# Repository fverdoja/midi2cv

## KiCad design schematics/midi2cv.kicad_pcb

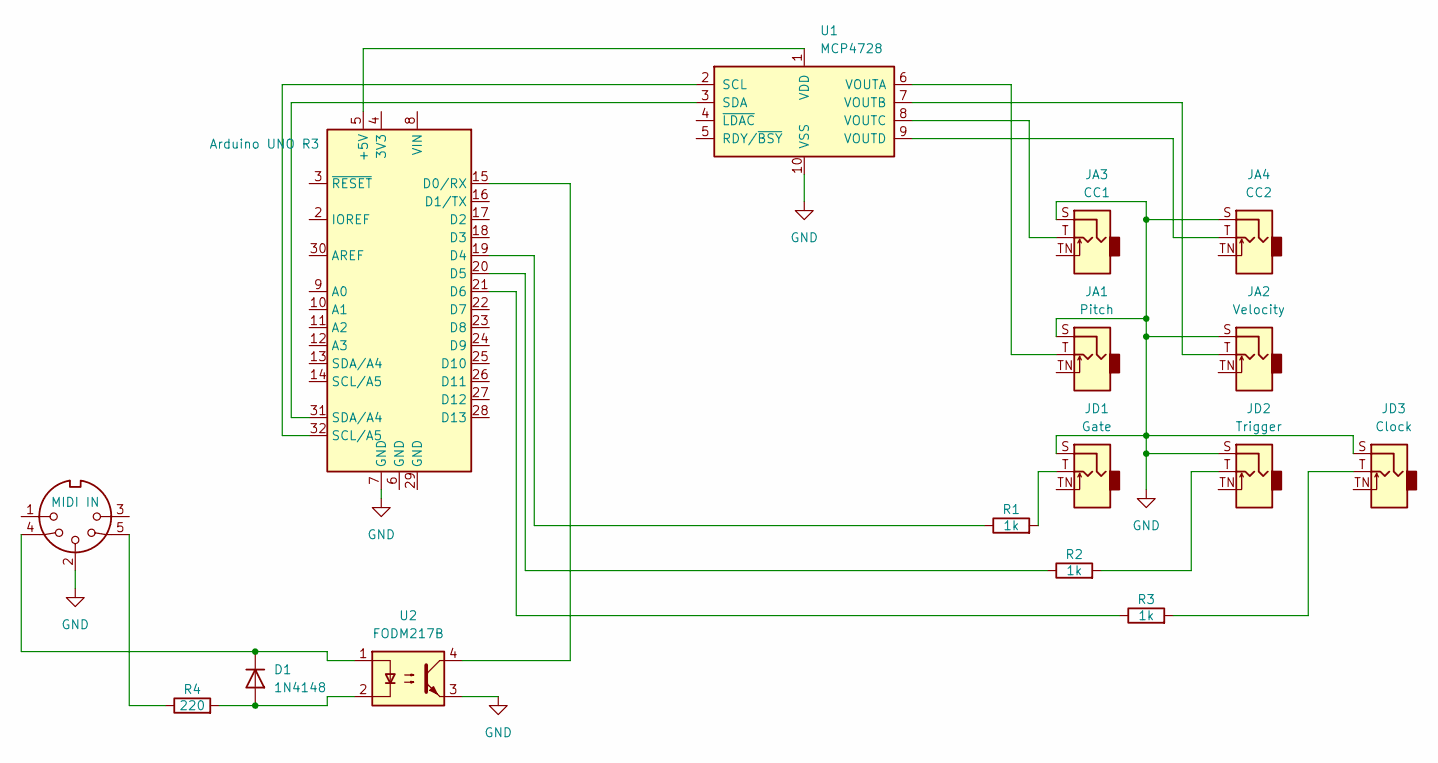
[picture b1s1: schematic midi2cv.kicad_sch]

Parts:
A1: Arduino UNO R3; Arduino_UNO_R3
D1: 1N4148; D_DO-35_SOD27_P7.62mm_Horizontal
JA1: Pitch; Jack_3.5mm_QingPu_WQP-PJ398SM_Vertical_CircularHoles
JA2: Velocity; Jack_3.5mm_QingPu_WQP-PJ398SM_Vertical_CircularHoles
JA3: CC1; Jack_3.5mm_QingPu_WQP-PJ398SM_Vertical_CircularHoles
JA4: CC2; Jack_3.5mm_QingPu_WQP-PJ398SM_Vertical_CircularHoles
JD1: Gate; Jack_3.5mm_QingPu_WQP-PJ398SM_Vertical_CircularHoles
JD2: Trigger; Jack_3.5mm_QingPu_WQP-PJ398SM_Vertical_CircularHoles
JD3: Clock; Jack_3.5mm_QingPu_WQP-PJ398SM_Vertical_CircularHoles
M1: MIDI IN; PinHeader_1x03_P1.00mm_Vertical
R1, R2, R3: 1k; R_Axial_DIN0411_L9.9mm_D3.6mm_P15.24mm_Horizontal
R4: 220; R_Axial_DIN0411_L9.9mm_D3.6mm_P15.24mm_Horizontal
U1: MCP4728; MSOP-10_3x3mm_P0.5mm
U2: FODM217B; SOP-4_4.4x2.6mm_P1.27mm

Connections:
GND: A1.7 (GND), JA1.S, JA2.S, JA3.S, JA4.S, JD1.S, JD2.S, JD3.S, M1.2, U1.10 (VSS), U2.3
unnamed: A1.5 (+5V), U1.1 (VDD)
unnamed: A1.15 (D0/RX), U2.4
unnamed: A1.19 (D4), R1.1
unnamed: A1.20 (D5), R2.1
unnamed: A1.21 (D6), R3.1
unnamed: D1.2 (A), R4.2, U2.2
unnamed: D1.1 (K), M1.4, U2.1
unnamed: JD1.T, R1.2
unnamed: JD2.T, R2.2
unnamed: JD3.T, R3.2
unnamed: M1.5, R4.1
unnamed: A1.32 (SCL/A5), U1.2 (SCL)
unnamed: A1.31 (SDA/A4), U1.3 (SDA)
unnamed: JA1.T, U1.6 (VOUTA)
unnamed: JA2.T, U1.7 (VOUTB)
unnamed: JA3.T, U1.8 (VOUTC)
unnamed: JA4.T, U1.9 (VOUTD)

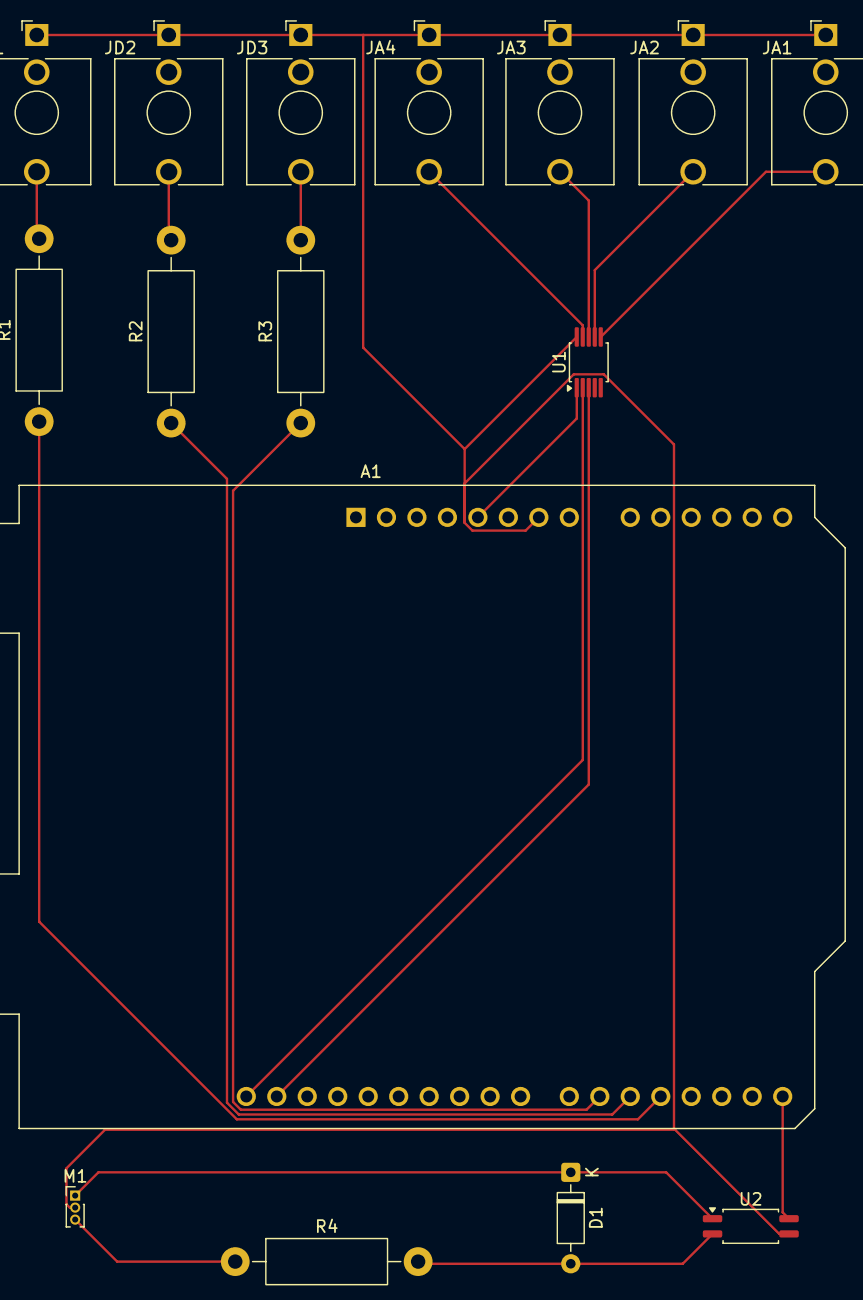
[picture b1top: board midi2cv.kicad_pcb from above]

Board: 2 copper layers, 16 parts (0 on the bottom side), 18 nets.

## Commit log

2026-03-08 first version
2026-03-08 cleaner formatting
